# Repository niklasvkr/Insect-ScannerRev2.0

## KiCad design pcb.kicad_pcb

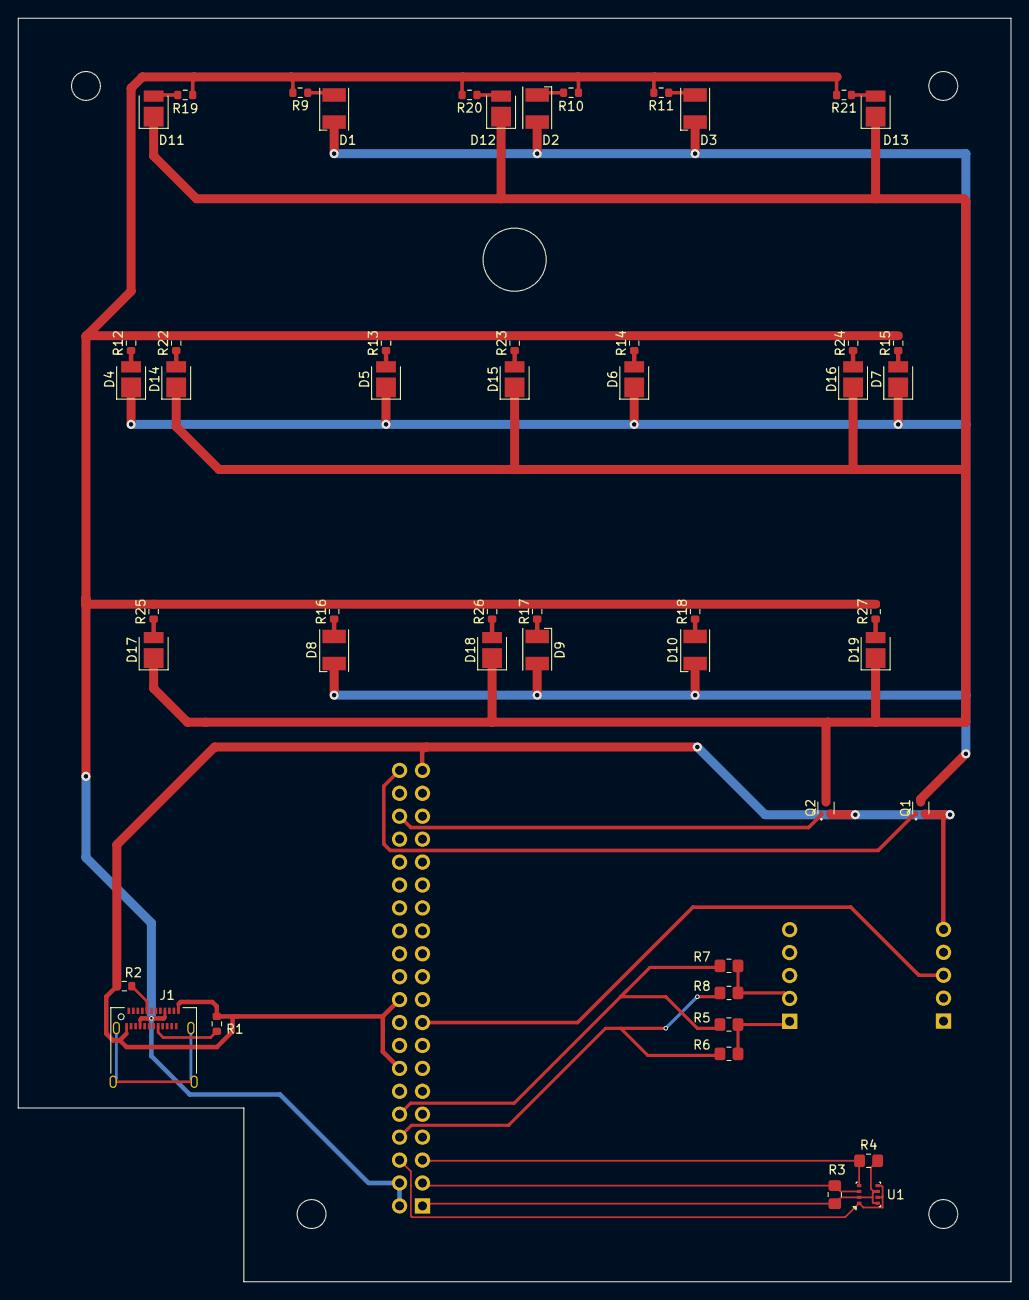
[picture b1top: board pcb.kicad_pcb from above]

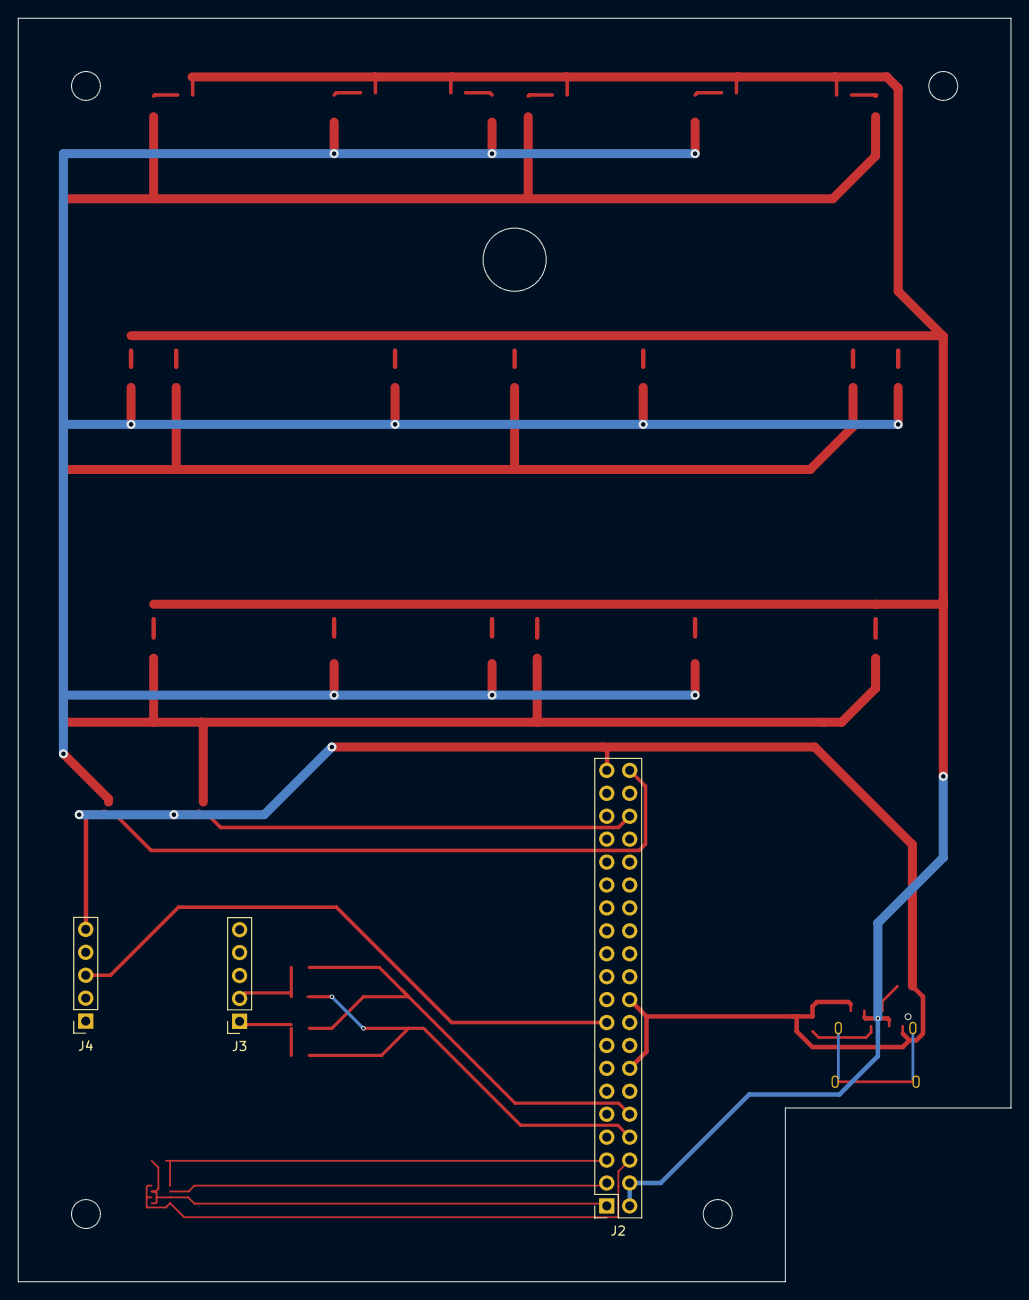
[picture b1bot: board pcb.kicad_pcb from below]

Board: 2 copper layers, 110.0 x 140.0 mm, 53 parts (3 on the bottom side), 34 nets.

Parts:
D1, D3, D8, D10: LED_405; LED_PLCC-2_3.4x3.0mm_KA
D2, D9: LED_blue; LED_PLCC-2_3.4x3.0mm_AK
D4, D5, D6, D7: LED_365; LED_PLCC_2835
D11, D12, D13, D14, D15, D16, D17, D18, D19: LED_w; LED_PLCC_2835
J1: USB_C_Receptacle_PowerOnly_6P; USB_C_Receptacle_Amphenol_12401610E4-2A
J2: Conn_02x20_Odd_Even; PinSocket_2x20_P2.54mm_Vertical
J3, J4: Conn_01x05_Socket; PinSocket_1x05_P2.54mm_Vertical
Q1, Q2: DMG1012T; SOT-523
R1, R2: 5k1; R_0603_1608Metric
R3, R4: 4k7; R_0805_2012Metric_Pad1.20x1.40mm_HandSolder
R5, R6, R7, R8: 0R; R_0805_2012Metric_Pad1.20x1.40mm_HandSolder
R9, R11, R16, R18: 56R; R_0603_1608Metric
R10, R17: 43R; R_0603_1608Metric
R12, R13, R14, R15: 51R; R_0603_1608Metric
R19, R20, R21, R22, R23, R24, R25, R26, R27: 68R; R_0603_1608Metric
U1: BME280; Bosch_LGA-8_2.5x2.5mm_P0.65mm_ClockwisePinNumbering

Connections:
+3.3V: J2.1, J2.17, J4.3, R3.1, R4.1, U1.2 (CSB), U1.6 (VDDIO), U1.8 (VDD)
+5V: J1.A9 (VBUS), J1.B9 (VBUS), J2.2, J2.4, R9.2, R10.2, R11.2, R12.2, R13.2, R14.2, R15.2, R16.2, R17.2, R18.2, R19.2, R20.2, R21.2, R22.2, R23.2, R24.2, R25.2, R26.2, R27.2
GND: J1.A12 (GND), J1.B12 (GND), J2.6, J2.9, J2.14, J2.20, J2.25, J2.30, J2.34, J2.39, J4.5, Q1.2 (S), Q2.2 (S), R1.1, R2.1, U1.1 (GND), U1.5 (SDO), U1.7 (GND)
unnamed: D1.2 (A), R9.1
unnamed: D1.1 (K), D2.1 (K), D3.1 (K), D4.1 (K), D5.1 (K), D6.1 (K), D7.1 (K), D8.1 (K), D9.1 (K), D10.1 (K), Q1.3 (D)
unnamed: D2.2 (A), R10.1
unnamed: D3.2 (A), R11.1
unnamed: D4.2 (A), R12.1
unnamed: D5.2 (A), R13.1
unnamed: D6.2 (A), R14.1
unnamed: D7.2 (A), R15.1
unnamed: D8.2 (A), R16.1
unnamed: D9.2 (A), R17.1
unnamed: D10.2 (A), R18.1
unnamed: D11.2 (A), R19.1
unnamed: D11.1 (K), D12.1 (K), D13.1 (K), D14.1 (K), D15.1 (K), D16.1 (K), D17.1 (K), D18.1 (K), D19.1 (K), Q2.3 (D)
unnamed: D12.2 (A), R20.1
unnamed: D13.2 (A), R21.1
unnamed: D14.2 (A), R22.1
unnamed: D15.2 (A), R23.1
unnamed: D16.2 (A), R24.1
unnamed: D17.2 (A), R25.1
unnamed: D18.2 (A), R26.1
unnamed: D19.2 (A), R27.1
unnamed: J1.A5 (CC1), R2.2
unnamed: J1.B5 (CC2), R1.2
unnamed: J3.1, R5.2, R6.2
unnamed: J3.2, R7.2, R8.2
RX: J2.10, R5.1, R7.1
SCL: J2.5, R4.2, U1.4 (SCK)
SDA: J2.3, R3.2, U1.3 (SDI)
TX: J2.8, R6.1, R8.1
led_uv_enable: J2.40, Q1.1 (G)
led_white_enable: J2.36, Q2.1 (G)

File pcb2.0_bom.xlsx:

Comment | Designator | Footprint
LED_w | D12,D11,D18,D19,D15,D16,D13,D14,D17 | LED_PLCC_2835
56R | R11,R16,R9,R18 | R_0603_1608Metric
68R | R27,R21,R26,R25,R20,R24,R23,R22,R19 | R_0603_1608Metric
DMG1012T | Q1,Q2 | SOT-523
0R | R6,R7,R8,R5 | R_0805_2012Metric_Pad1.20x1.40mm_HandSolder
5k1 | R2,R1 | R_0603_1608Metric
LED_365 | D5,D4,D7,D6 | LED_PLCC_2835
43R | R17,R10 | R_0603_1608Metric
LED_405 | D8,D1,D3,D10 | LED_PLCC-2_3.4x3.0mm_KA
LED_blue | D2,D9 | LED_PLCC-2_3.4x3.0mm_AK
4k7 | R4,R3 | R_0805_2012Metric_Pad1.20x1.40mm_HandSolder
51R | R13,R12,R14,R15 | R_0603_1608Metric
BME280 | U1 | Bosch_LGA-8_2.5x2.5mm_P0.65mm_ClockwisePinNumbering
USB_C_Receptacle_PowerOnly_6P | J1 | USB_C_Receptacle_Amphenol_12401610E4-2A
100nF | C1 | C_0603_1608Metric
Conn_02x20_Odd_Even | J2 | PinSocket_2x20_P2.54mm_Vertical
Conn_01x05_Socket | J4,J3 | PinSocket_1x05_P2.54mm_Vertical

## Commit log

2024-12-10 Schaltplan sensorpcb hinzugefügt und Schaltplan pcb, bom bearbeitet
2025-02-26 Update Schaltplan
